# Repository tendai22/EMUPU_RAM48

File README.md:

# EMUPU_RAM48
A retroCPU companion board, inspired by Denno-Densetsu EMUZ80 and its related/inspired works

PIC18F, 128kB SRAMといにしえのCPUを用いて、いにしえのCPUを動作させます。Z80ピンアサインを基本にしていますが、基板上部にレトロCPUを載せた小型基板(メザニン基板)を繋ぐことで、Z80以外のさまざまなCPUに対応できるようにします。

PIC18F57Q43のCLC(Configurable Logic Cell)を活かしてCPU/SRAM制御信号を生成することで、最高パフォーマンスを目指します。そのために、アクセスタイム12nsのSRAMを使用します。48pin PICでピン数を稼いで、SPI経由でSDカードを駆動することも目標とする。

回路的には[奥江さんの作品](https://github.com/satoshiokue/SuperMEZ80)に由来しています。但し、奥江さんの作品は[EMUZ80](https://github.com/vintagechips/emuz80)基板をベースにしておりメザニン基板上でSRAMとCPUを搭載するのに対し、この試みでは、SRAMをメイン基板に移し、メザニン基板上にはCPUだけを載せるようにしています。

## コンセプト

* レトロCPUのプログラムはSRAM上に展開する。
* レトロCPUのプログラム展開はPICが行う(ブートローディング機能)。
* レトロCPUからSRAMへのアクセスは、/OE, /WEで行うが、これらの信号はPICのCLCで生成する。
* レトロCPUのI/OアクセスはPICで受ける。タイミング合わせのため、バスサイクルを延長する。
* バスサイクルの延長: Z80の場合は/WAIT信号による。68008の場合は/DTACKを使う。いずれもCLCでソフトウェア介在なしで発生する。
* I/O空間にはシリアル(Data, Status)、ディスクアクセス用のポートを置く。
* 割り込み発生とアクノレッジサイクル対応もPICが行う。

## CLCの使い方

SRAMの/OE, /WEをCLCでハード的に(ソフトを介在する必要なしに)発生する。これにより、SRAMアクセス時はソフト処理のオーバヘッドなしにZ80のメモリサイクルを実行させることができる。

I/Oアクセスは従来通り、PICがZ80のI/Oサイクルに対応する。/IORQで/WAIT信号をアサートし、I/OアクセスでCPUはアクセスを延長する。このやり方により、I/Oアクセスは時間が掛かる(数us～10数us程度)が、Z80プログラムの実行速度の大部分はメモリアクセスによるため、パフォーマンス低下の影響は小さいとしてよいだろう。

PIC側ソフトでI/O処理を行い、完了すると/BUSRQを立てて/WAITをネゲートする。CPUがI/Oサイクルを終了する(/IORQを監視している)と、/BUSRQを落としてCPUの実行を再開させる。/BUSRQをこのように使うことで、PIC側のサイクル終了処理を完了させるまでZ80を次のサイクルに入れないようにすることができる。

* CLCは3個使用する。それぞれで /OE, /WE, /WAITを発生する。
* /OE = /MREQ == 0 && /RD == 0 && /RFSH == 1
* /WE = /MREQ == 0 && /RD == 1 && /RFSH == 1
* /WAIT は/IORQの下りエッジでセットされるD-FFの/Q出力をあてる。

CLC1,2,3を使用し、それぞれの出力を、CLC1: /OE, CLC2: /WE, CLC3: /WAIT と割り当てる。

CLC1, CLC2は 4input AND, CLC3は D-FF with R/S とする。

CLC全セルの入力は最大8本で、RA/RCから4本、RB/RDから4本割り当てることができる。RE, RFからの割り当てはできない。この制約を考慮すると、
* Z80の出力, PICの入力: RA, RBに割り当てる。
* Z80の入力, PICの出力: RE(ソフト制御), RA or RB (CLC出力)

に割り当てるという原則ができる。

CLC1, CLC2の入力は、/MREQ, /RD, /RFSH であり、それぞれ RA1, RA4, RA5 に接続する。

CLC3の D-FF CLKに /IORQ を割り当てる。/IORQ を RA0に接続する。D-FF /Q出力を /WAITにつなぐ。/WAITをRB7に接続する。

以上を考慮して、Z80の制御線をPICに以下のように割り当てた(Rev.002.1)。

|PIC signal|Z80 signal|
|--|--|
|RA0|IORQ|
|RA1|MREQ|
|RA2|SRAM WE|
|RA3|CLK|
|RA4|SRAM OE|
|RA5|RD|
|RB7|WAIT|
|RB6|TEST(ソフト駆動用)|
|RB5|M1|
|RB4|RFSH|
|RE0|BUSRQ|
|RE1|RESET|
|RE2|INT|

RB0-3はSDカード接続用に割り当てた。

> Z80版では/RDが/MREQの下りエッジよりも先に確定することを前提としている。データシート的にはこの前提が成立するかどうか不明である。この前提が成立しない場合、リードサイクルの最初に /WEに一瞬グリッジが発生する可能性がある。このグリッジによりSRAM中のデータが破壊される可能性がある。ライトサイクルは本来/WR信号でタイミングを取る。この場合、RD7に/WR信号を繋いで、/WE信号のゲート(CLC2)入力に/WR信号を入れることになる。

## ブートローディング

SRAMのアドレスバスにPICのRD0-7, RF0-7を割り当てできている。よって、任意の位置にプログラムを転送することができる。PICからSRAMへの書き込みは、
* アドレスをRD, RFに出力し、
* データをRCに出力し、
* /WEをアサートし、ネゲートする

ことで実現できる。

> PICがアドレスバスにピン割り当てできない場合は、リセット解除後のメモリリードサイクルを捕まえて、0x21, (デスティネーション下位), (デスティネーション上位), 0x36, (書き込みバイト１バイト目), 0x23, 0x36, (書き込みバイト2バイト目), 0x23, 0x36, ... と順次バイトを置いてゆくことでSRAMにデータを転送することができる(「命令置き」)。

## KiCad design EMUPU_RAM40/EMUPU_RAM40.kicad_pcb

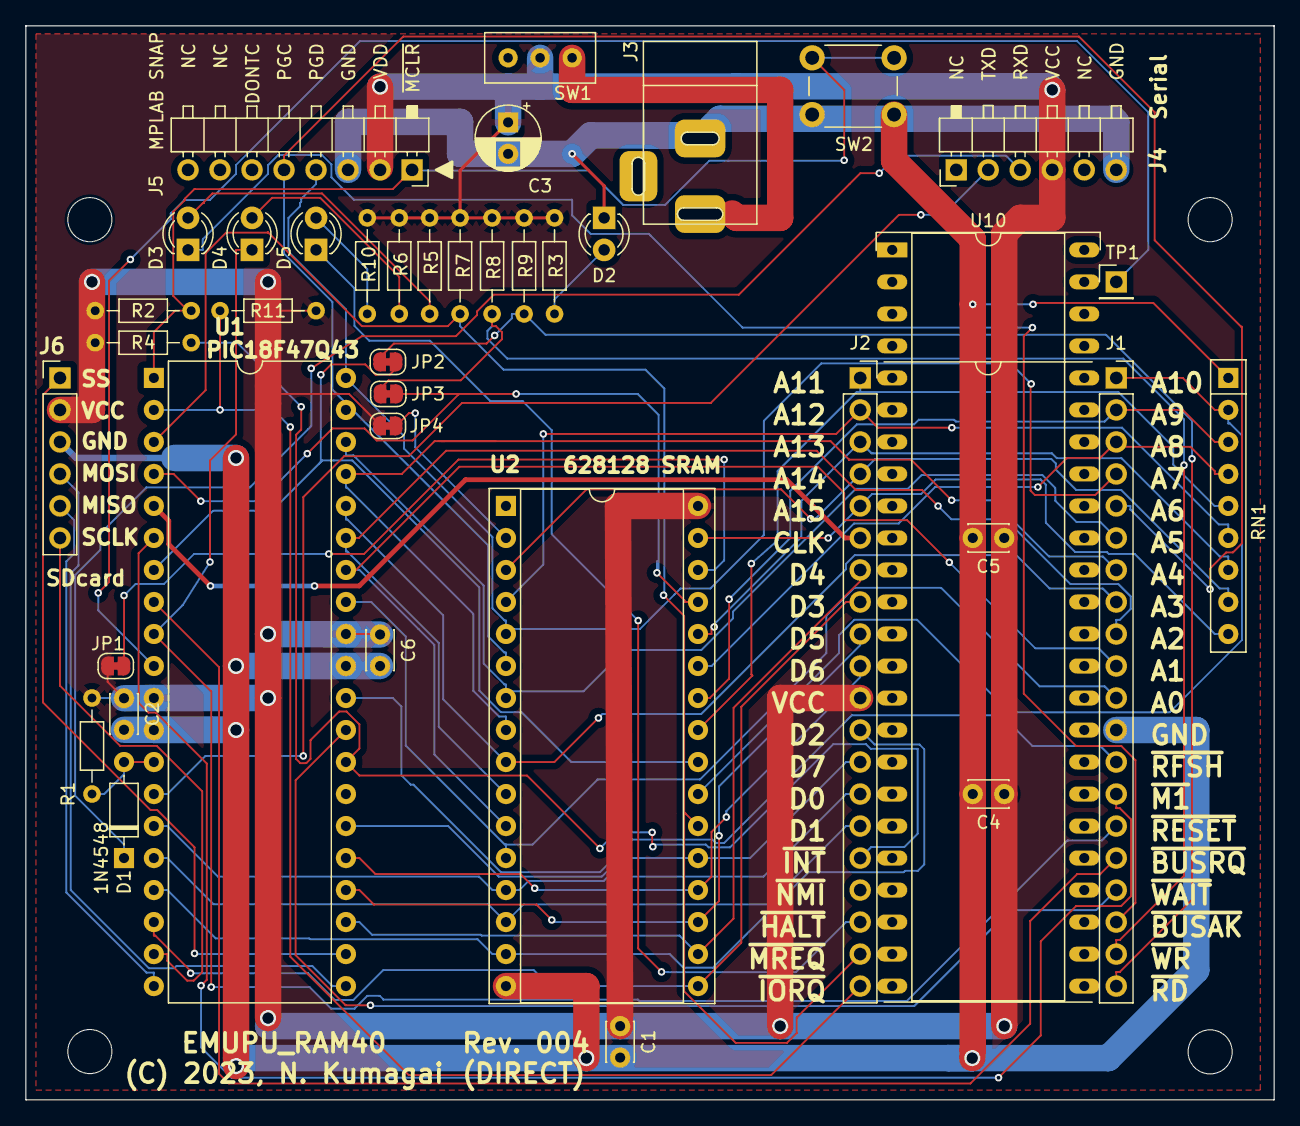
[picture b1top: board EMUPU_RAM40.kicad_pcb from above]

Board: 2 copper layers, 99.1 x 85.2 mm, 43 parts (0 on the bottom side), 57 nets.

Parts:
C1, C2, C4, C5, C6: 0.1uF; C_Disc_D3.0mm_W2.0mm_P2.50mm
C3: 10uF; CP_Radial_D5.0mm_P2.50mm
D1: 1N4148; D_DO-35_SOD27_P7.62mm_Horizontal
D2: LED; LED_D3.0mm
D3: BUSAK; LED_D3.0mm
D4: RESET; LED_D3.0mm
D5: HALT; LED_D3.0mm
H2, H4, H5, H6: MountingHole; MountingHole_3.5mm
J1, J2: Conn_01x20_Socket; PinSocket_1x20_P2.54mm_Vertical
J3: Barrel_Jack_Switch; BARREL_JACK
J4: Conn_01x06_Pin; PinHeader_1x06_P2.54mm_Horizontal_NoFeet
J5: Conn_01x08_Pin; PinHeader_1x08_P2.54mm_Rev_Horizontal_Nofoot
J6: Conn_01x06_Pin; PinHeader_1x06_P2.54mm_Vertical
JP1, JP2, JP3, JP4: SolderJumper_2_Bridged; SolderJumper-2_P1.3mm_Bridged_RoundedPad1.0x1.5mm
R1, R2, R4, R7, R8, R9, R11: 10k; R_Axial_DIN0204_L3.6mm_D1.6mm_P7.62mm_Horizontal
R3, R5, R6, R10: 1.5k; R_Axial_DIN0204_L3.6mm_D1.6mm_P7.62mm_Horizontal
RN1: R_Network08; R_Array_SIP9
SW1: SW_SPDT; PowerSW_for_SBC_series
SW2: SW_SPST; SW_PUSH_6mm_H4.3mm
TP1: TEST; PinHeader_1x01_P2.54mm_Vertical
U1: PIC18F47Q43-IP; DIP-40_W15.24mm
U2: 628128; DIP-32_W15.24mm_Socket
U10: DIP-48_W15.24mm_Socket_OvalPad_nocourtyard; DIP-48_W15.24mm_Socket_OvalPad_splitcouryard

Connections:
/A0: J1.11, U1.33 (RB0), U2.12 (A0)
/A1: J1.10, U1.34 (RB1), U2.11 (A1)
/A2: J1.9, U1.35 (RB2), U2.10 (A2)
/A3: J1.8, U1.36 (RB3), U2.9 (A3)
/A4: J1.7, U1.37 (RB4), U2.8 (A4)
/A5: J1.6, U1.38 (RB5), U2.7 (A5)
/A6: J1.5, J5.5, U1.39 (ICSPCLK/RB6), U2.6 (A6)
/A7: J1.4, J5.4, U1.40 (ICPSDAT/RB7), U2.5 (A7)
/A8: J1.3, RN1.4 (R3), U2.27 (A8)
/A9: J1.2, RN1.3 (R2), U2.26 (A9)
/A10: J1.1, RN1.2 (R1), U2.23 (A10)
/CLK: J2.6, U1.5 (RA3)
/D0: J2.14, U1.15 (RC0), U2.13 (Q0)
/D1: J2.15, U1.16 (RC1), U2.14 (Q1)
/D2: J2.12, U1.17 (RC2), U2.15 (Q2)
/D3: J2.8, U1.18 (RC3), U2.17 (Q3)
/D4: J2.7, U1.23 (RC4), U2.18 (Q4)
/D5: J2.9, U1.24 (RC5), U2.19 (Q5)
/D6: J2.10, U1.25 (RC6), U2.20 (Q6)
/D7: J2.13, U1.26 (RC7), U2.21 (Q7)
/MISO: J6.5, U1.20 (RD1)
/MOSI: J6.4, U1.21 (RD2)
/SCLK: J6.6, U1.19 (RD0)
/SS: J6.1, U1.22 (RD3)
/TEST: TP1.1, U1.10 (RE2)
/~BUSAK: D3.1 (K), J1.18
/~BUSRQ: J1.16, U1.8 (RE0)
/~HALT: D5.1 (K), J2.18
/~INT: J2.16, R4.2, U1.28 (RD5)
/~IORQ: J2.20, R11.2, U1.2 (RA0)
/~M1: J1.14, U1.6 (RA4)
/~MREQ: J2.19, R7.2, U1.3 (RA1), U2.22 (~CS1)
/~RD: J1.20, JP2.1 (A), R9.2
/~RESET: D4.1 (K), J1.15, U1.9 (RE1)
/~RFSH: J1.13, U1.30 (RD7)
/~WAIT: J1.17, U1.29 (RD6)
/~WR: J1.19, JP3.1 (A), R8.2
GND: C1.2, C2.2, C3.2, C4.2, C5.2, C6.2, D2.1 (K), J1.12, J3.2, J4.6, J5.3, J6.3, RN1.1 (common), SW2.2 (B), U1.12 (VSS), U1.31 (VSS), U2.16 (GND)
unnamed: D1.2 (A), R1.2, U1.13 (RA7)
unnamed: D1.1 (K), J4.3
unnamed: D2.2 (A), R3.2
unnamed: D3.2 (A), R5.2
unnamed: D4.2 (A), R6.2
unnamed: D5.2 (A), R10.2
unnamed: J2.1, RN1.5 (R4), U2.25 (A11)
unnamed: J2.2, RN1.6 (R5), U2.4 (A12)
unnamed: J2.3, RN1.7 (R6), U2.28 (A13)
unnamed: J2.4, RN1.8 (R7), U2.3 (A14)
unnamed: J2.5, RN1.9 (R8), U2.31 (A15)
unnamed: J4.2, U1.14 (RA6)
unnamed: J5.1, R2.2, SW2.1 (A), U1.1 (~MCLR)
unnamed: JP1.1 (A), U2.30 (CS2)
unnamed: JP2.2 (B), U1.7 (RA5), U2.24 (~OE)
unnamed: JP3.2 (B), U1.4 (RA2), U2.29 (~WE)
unnamed: JP4.1 (A), U2.2 (A16)
unnamed: J3.1, SW1.3 (C)
VCC: C1.1, C2.1, C3.1, C4.1, C5.1, C6.1, J2.11, J4.4, J5.2, J6.2, JP1.2 (B), JP4.2 (B), R1.1, R2.1, R3.1, R4.1, R5.1, R6.1, R7.1, R8.1, R9.1, R10.1, R11.1, SW1.2 (B), U1.11 (VDD), U1.32 (VDD), U2.32 (VCC)

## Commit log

2023-02-25 Initial, but checked, finished, ready to send Garber files
2023-02-25 Adjusting rule, described in Kosakas book, need some refinements
2023-02-25 Add Beta-filling, archive ZIP file
2023-02-25 Generate garber files
2023-02-26 Add Z80 label, RBx jumpers, garbers, ZIP
2023-02-26 Ordered version, designated as Rev. 001
2023-02-26 EMUPC_RAM40 start, add kicad_sch and kicad_pcb files
2023-02-27 Add pdf schematic files
2023-02-27 ram40 powerlines comleted, ready to start autoroute
2023-02-27 before autorouting 2nd version, 48pin dummy socket included
2023-02-27 3rd before-freerouting, add Z80 pin-names, beta-border, and narrower board size and rearrangement of parts
2023-02-27 Loose some unconnected VCC/GND, move some Rs
2023-02-27 Correct Serial 6pin connections
2023-02-27 fix some on schematics
2023-02-27 Fix J4 silk, add pin names on J4, J5, fix vcc connection bottom of SRAM
2023-02-28 EMUPU_RAM40 PCB finished
2023-02-28 fix garber files, order it to JLCPCB
2023-02-28 schematic pdf, Rev100.pdf
2023-02-28 EMUPU_RAM68k schematic and 68008 device symbol
2023-02-28 Add RAM68k schematic pdf file
2023-03-03 Exchange RD6 and RD7, add .gitignore
2023-03-04 ram40_68k8 for B-board Rev. 002, just rebulided.
2023-03-09 Cut BR-PIC RD5, and add TEST pin
2023-03-16 Fix BARREL_JACK footpattern, modify schematic file (Rev002), pcb file fix ongoing
2023-03-16 New (Rev002) netlist just imported
2023-03-16 EMUPU_RAM48_Rev002. pcb modifying completed
2023-03-16 RAM48 pcb slightly revised
2023-03-22 change revision number in schematic file., add PDF file
2023-03-22 Describe pin assign idea in README.md
2023-03-29 slightly modified to Rev.002
2023-04-01 Ordered JLCPCB, ram48_rev002.2
2023-05-13 under construction for Rev003 done the follows * fix PowerPlug pin assignment * change /MREQ, /RD, /WR for full_direct * A jumper is assigned to SRAM CS2 (now pulled-up) * add jumpers on /MREQ, /RD, 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
    remains for the following
    * add TEST pin
    * add LEDs and resistors, including RESET, BUSACK, and HALT
    * add pull down resistors to A15-A8, as needed.* add some jumpers for SDcard controls (A9-A12)
    * add four jumpers for SDcard (A9-A12)
    After confirming 8byte rewrite and reset bootloading, I will finishes the remains.
2023-05-14 Rev003: arrange new footprints, before autorouting
2023-05-14 Rev003: autorouting done, no no-connection, but some error/warning remains
2023-05-15 Rev003: some mod, still Rev# 001 remains, need to update
2023-05-15 Rev003: ordered to JLCPCB
2023-05-17 removed *.net, fp-info-cache
2023-05-17 RAM48-Rev003: direct ready for production
2023-05-28 Rev004, add 10k pullup resister to IORQ
2023-06-14 rm unnecessry files, and add Z8S180_57Q.* files

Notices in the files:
EMUPU_RAM40/EMUPU_RAM40.kicad_pcb:
(C) 2023, N. Kumagai
